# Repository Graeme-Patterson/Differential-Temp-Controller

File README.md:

# Differential-Temp-Controller

This is my differential temperature controller with Wi-Fi interface and Touch screen.

The idea behind this controller was to minimise the heating cost of keeping my workshop/mancave warm in Canberra Australia winters. After recently installing a solar electricity system on our house my thoughts were about how I could use the heat from the sun to warm my workshop.
The design was to heat air in long black plastic tubes mounted in a glass fronted box in a sunny location on the roof or wall of the workshop and use a low voltage fan to move air from outside, through the plastic tubes to warm the air and blow this into the workshop. To ensure that heating is achieved and to accound for any temperature drop getting the warmed air into the workshop, I needed a device that measured the temperature at the source and at the destination. I also wanted to have control over the device from inside my house and local control with visual display.

The final result uses a 2.8" ILI9341 TFT SPI display sourced from eBay (China) and an ESP8266/NodeMCU/ESP12-E device mounted on a custom PCB using a simple relay output to control a fan. Power is via a DC barrel connector (with ideas that this could be via Solar). The temperature sensors are low cost waterproof 10k NTC Thermistors, again sourced from eBay.

- [DTC Overview](/README.md)
- [How to make one](/HowToMake.md)
- [Operation instructions](/Operation.md)
- [Connecting it up](/connecting.md)

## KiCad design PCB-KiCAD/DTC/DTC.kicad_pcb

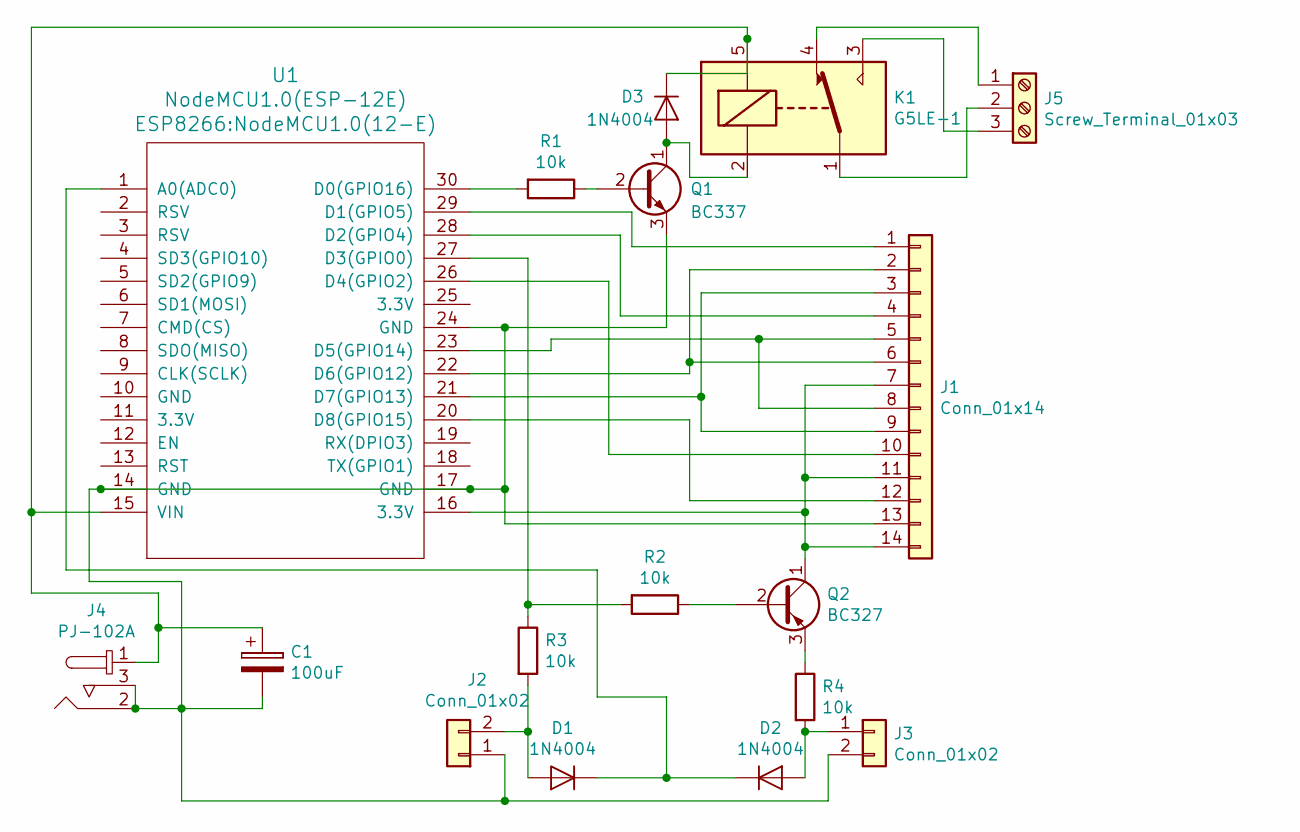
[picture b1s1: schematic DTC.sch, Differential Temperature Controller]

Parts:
C1: 100uF; CP_Radial_D8.0mm_P3.80mm
D1, D2, D3: 1N4004; D_DO-41_SOD81_P10.16mm_Horizontal
J1: Conn_01x14; Molex_KK-6410-14_14x2.54mm_Straight
J2, J3: Conn_01x02; Molex_KK-6410-02_02x2.54mm_Straight
J4: PJ-102A; Barrel_Jack_5.5mmODx2.1mmID_PJ-102A; MPN PJ-102A; Digi-Key_PN CP-102A-ND
J5: Screw_Terminal_01x03; TerminalBlock_bornier-3_P5.08mm
K1: G5LE-1; Relay_SPDT_OMRON-G5LE-1
Q1: BC337; TO-92-3_Formed_Leads
Q2: BC327; TO-92-3_Formed_Leads
R1, R2, R3, R4: 10k; R_Axial_DIN0204_L3.6mm_D1.6mm_P7.62mm_Horizontal
U1: NodeMCU1.0(ESP-12E); NodeMCU1.0(12-E)

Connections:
unnamed: C1.1, D3.1 (K), J4.1, K1.5, U1.15 (VIN)
unnamed: C1.2, J1.13, J2.1, J3.2, J4.2, J4.3, Q1.3 (E), U1.14 (GND), U1.17 (GND), U1.24 (GND)
unnamed: D1.1 (K), D2.1 (K), U1.1 (A0(ADC0))
unnamed: D1.2 (A), J2.2, R3.2
unnamed: D2.2 (A), J3.1, R4.2
unnamed: D3.2 (A), K1.2, Q1.1 (C)
unnamed: J1.1, U1.29 (D1(GPIO5))
unnamed: J1.2, J1.6, U1.22 (D6(GPIO12))
unnamed: J1.3, J1.9, U1.21 (D7(GPIO13))
unnamed: J1.4, U1.28 (D2(GPIO4))
unnamed: J1.5, J1.8, U1.23 (D5(GPIO14))
unnamed: J1.10, U1.26 (D4(GPIO2))
unnamed: J1.7, J1.11, J1.14, Q2.1 (C), U1.16 (3.3V)
unnamed: J1.12, U1.20 (D8(GPIO15))
unnamed: J5.1, K1.4
unnamed: J5.2, K1.1
unnamed: J5.3, K1.3
unnamed: Q1.2 (B), R1.1
unnamed: Q2.2 (B), R2.1
unnamed: Q2.3 (E), R4.1
unnamed: R1.2, U1.30 (D0(GPIO16))
unnamed: R2.2, R3.1, U1.27 (D3(GPIO0))

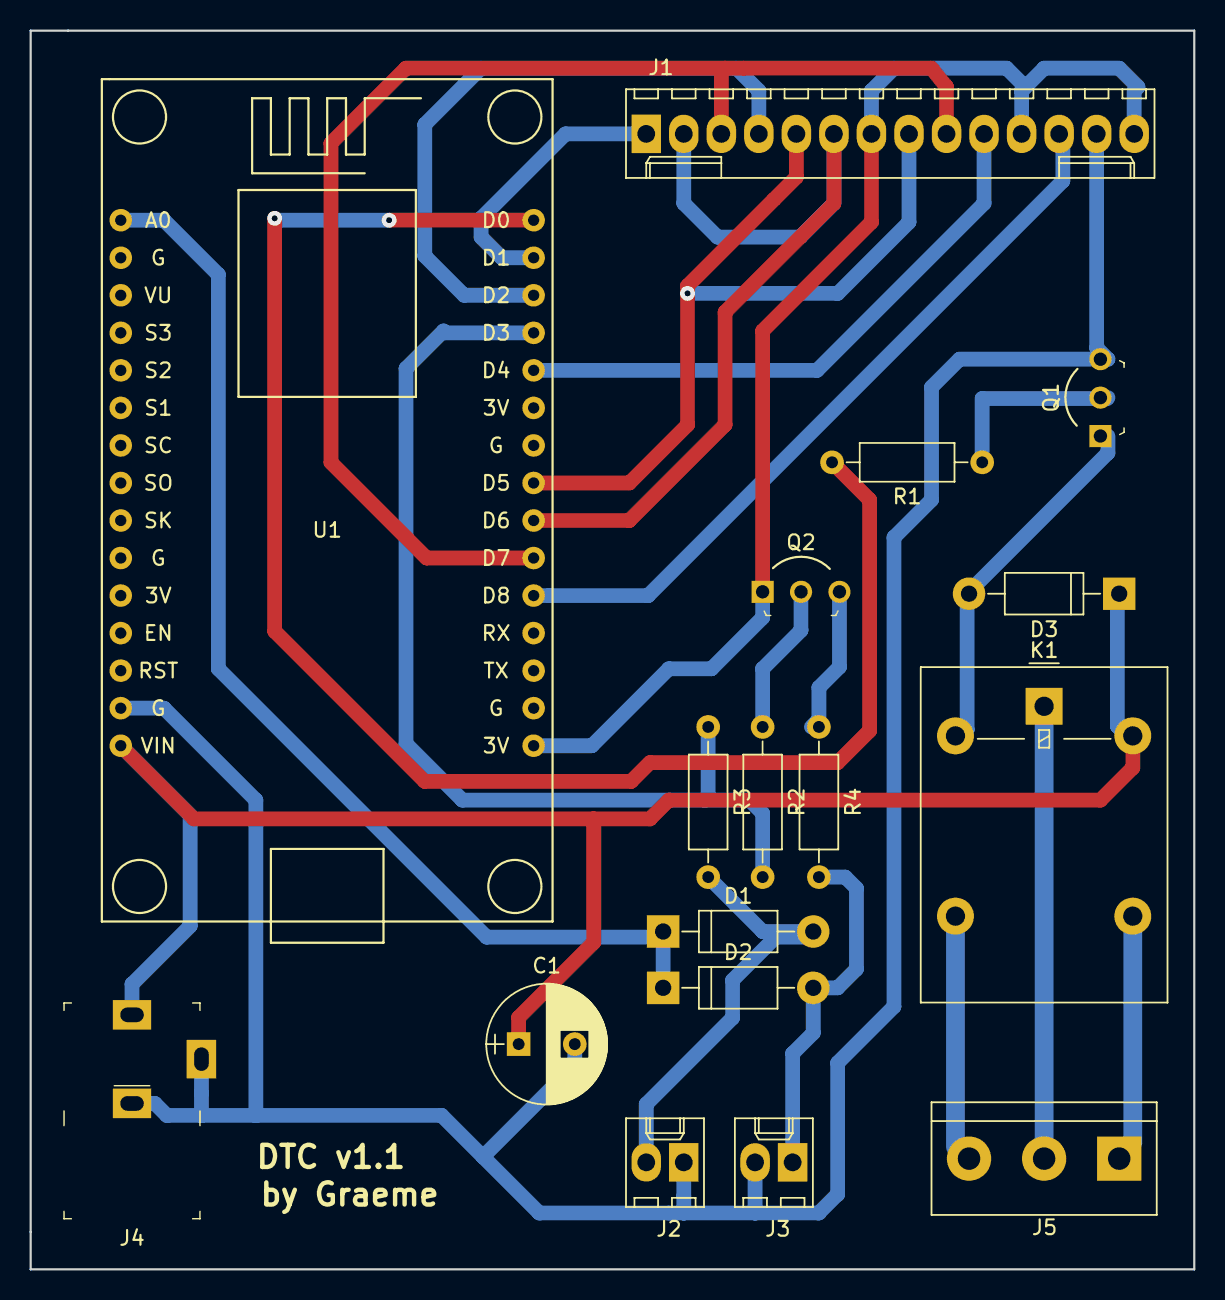
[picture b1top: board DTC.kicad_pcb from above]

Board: 2 copper layers, 78.7 x 83.8 mm, 17 parts (0 on the bottom side), 22 nets.

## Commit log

2020-12-30 Added PCB Files
    KiCAD PCB files
2020-12-30 Updated PCB
    Updated PCB and added pdf's of layers
2020-12-31 Added images
2020-12-31 Update Images
2020-12-31 changes to readme
2020-12-31 ReadMe updates
2020-12-31 How to files
2020-12-31 Documentation
2020-12-31 Create LICENSE
